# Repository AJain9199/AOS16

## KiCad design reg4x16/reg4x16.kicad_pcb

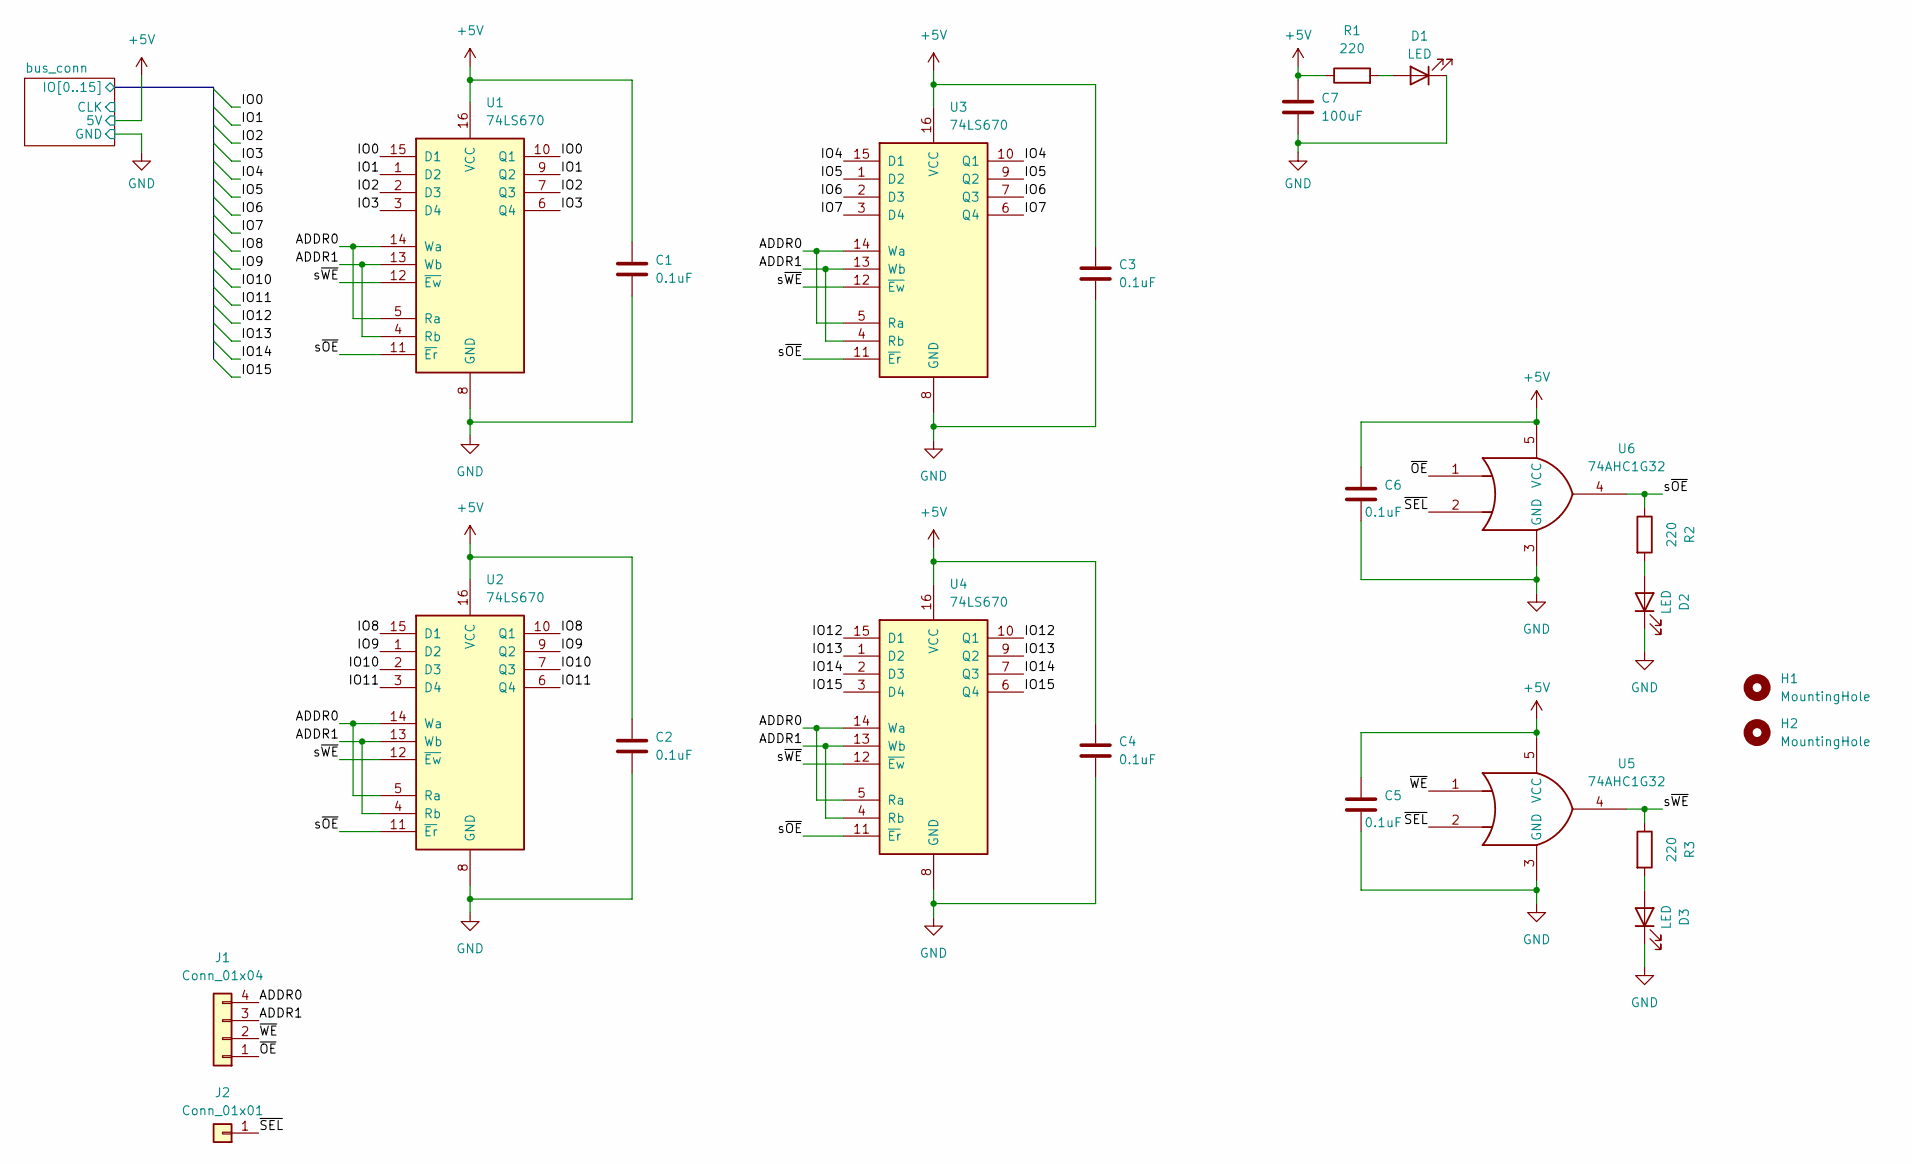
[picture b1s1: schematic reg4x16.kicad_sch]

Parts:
C1, C2, C3, C4, C5, C6: 0.1uF; C_0603_1608Metric
C7: 100uF; CP_Elec_5x5.3
D1, D2, D3: LED; LED_0603_1608Metric
H1, H2: MountingHole; MountingHole_2.2mm_M2
J1: Conn_01x04; PinHeader_1x04_P2.54mm_Vertical
J2: Conn_01x01; PinHeader_1x01_P2.54mm_Horizontal
R1, R2, R3: 220; R_0603_1608Metric
U1, U2, U3, U4: 74LS670; SOIC-16_3.9x9.9mm_P1.27mm
U5, U6: 74AHC1G32; SOT-23-5

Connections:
+5V: C1.1, C2.1, C3.1, C4.1, C5.1, C6.1, C7.1, R1.1, U1.16 (VCC), U2.16 (VCC), U3.16 (VCC), U4.16 (VCC), U5.5 (VCC), U6.5 (VCC); also elsewhere on the board
/ADDR0: J1.4, U1.5 (Ra), U1.14 (Wa), U2.5 (Ra), U2.14 (Wa), U3.5 (Ra), U3.14 (Wa), U4.5 (Ra), U4.14 (Wa)
/ADDR1: J1.3, U1.4 (Rb), U1.13 (Wb), U2.4 (Rb), U2.13 (Wb), U3.4 (Rb), U3.13 (Wb), U4.4 (Rb), U4.13 (Wb)
/bus_conn/IO0: U1.10 (Q1), U1.15 (D1); also elsewhere on the board
/bus_conn/IO1: U1.1 (D2), U1.9 (Q2); also elsewhere on the board
/bus_conn/IO2: U1.2 (D3), U1.7 (Q3); also elsewhere on the board
/bus_conn/IO3: U1.3 (D4), U1.6 (Q4); also elsewhere on the board
/bus_conn/IO4: U3.10 (Q1), U3.15 (D1); also elsewhere on the board
/bus_conn/IO5: U3.1 (D2), U3.9 (Q2); also elsewhere on the board
/bus_conn/IO6: U3.2 (D3), U3.7 (Q3); also elsewhere on the board
/bus_conn/IO7: U3.3 (D4), U3.6 (Q4); also elsewhere on the board
/bus_conn/IO8: U2.10 (Q1), U2.15 (D1); also elsewhere on the board
/bus_conn/IO9: U2.1 (D2), U2.9 (Q2); also elsewhere on the board
/bus_conn/IO10: U2.2 (D3), U2.7 (Q3); also elsewhere on the board
/bus_conn/IO11: U2.3 (D4), U2.6 (Q4); also elsewhere on the board
/bus_conn/IO12: U4.10 (Q1), U4.15 (D1); also elsewhere on the board
/bus_conn/IO13: U4.1 (D2), U4.9 (Q2); also elsewhere on the board
/bus_conn/IO14: U4.2 (D3), U4.7 (Q3); also elsewhere on the board
/bus_conn/IO15: U4.3 (D4), U4.6 (Q4); also elsewhere on the board
/s~OE: R2.1, U1.11 (~Er), U2.11 (~Er), U3.11 (~Er), U4.11 (~Er), U6.4
/s~WE: R3.1, U1.12 (~Ew), U2.12 (~Ew), U3.12 (~Ew), U4.12 (~Ew), U5.4
/~OE: J1.1, U6.1
/~SEL: J2.1, U5.2, U6.2
/~WE: J1.2, U5.1
GND: C1.2, C2.2, C3.2, C4.2, C5.2, C6.2, C7.2, D1.1 (K), D2.1 (K), D3.1 (K), U1.8 (GND), U2.8 (GND), U3.8 (GND), U4.8 (GND), U5.3 (GND), U6.3 (GND); also elsewhere on the board
unnamed: D1.2 (A), R1.2
unnamed: D2.2 (A), R2.2
unnamed: D3.2 (A), R3.2

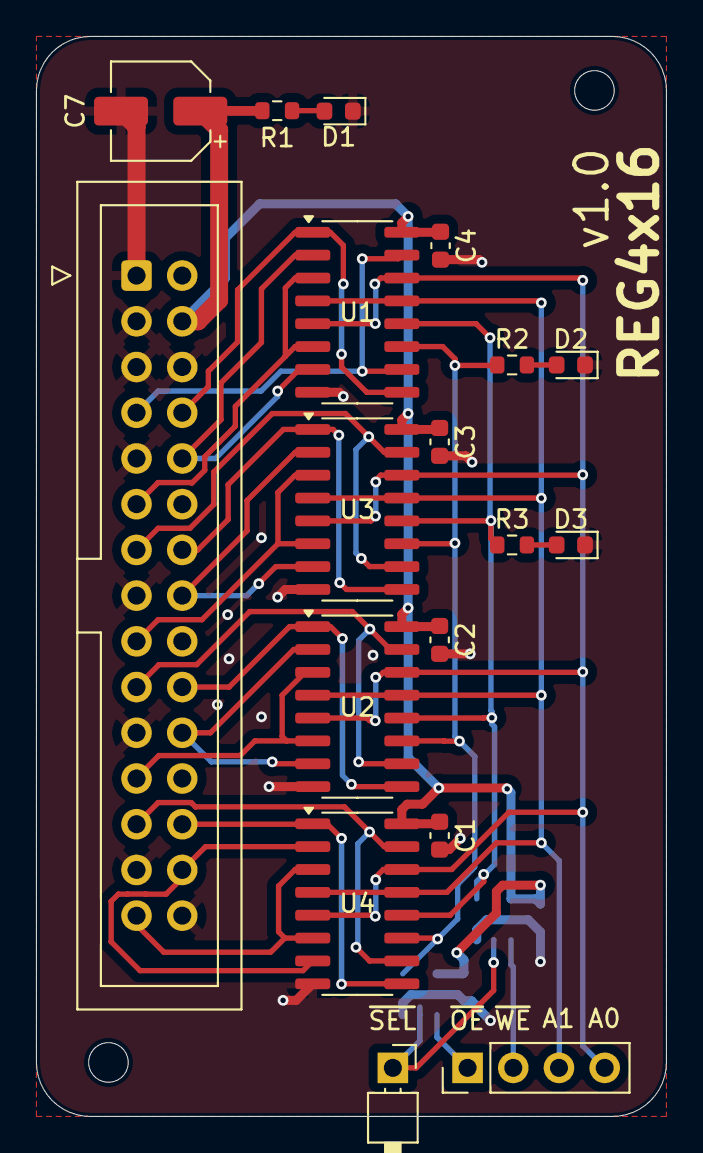
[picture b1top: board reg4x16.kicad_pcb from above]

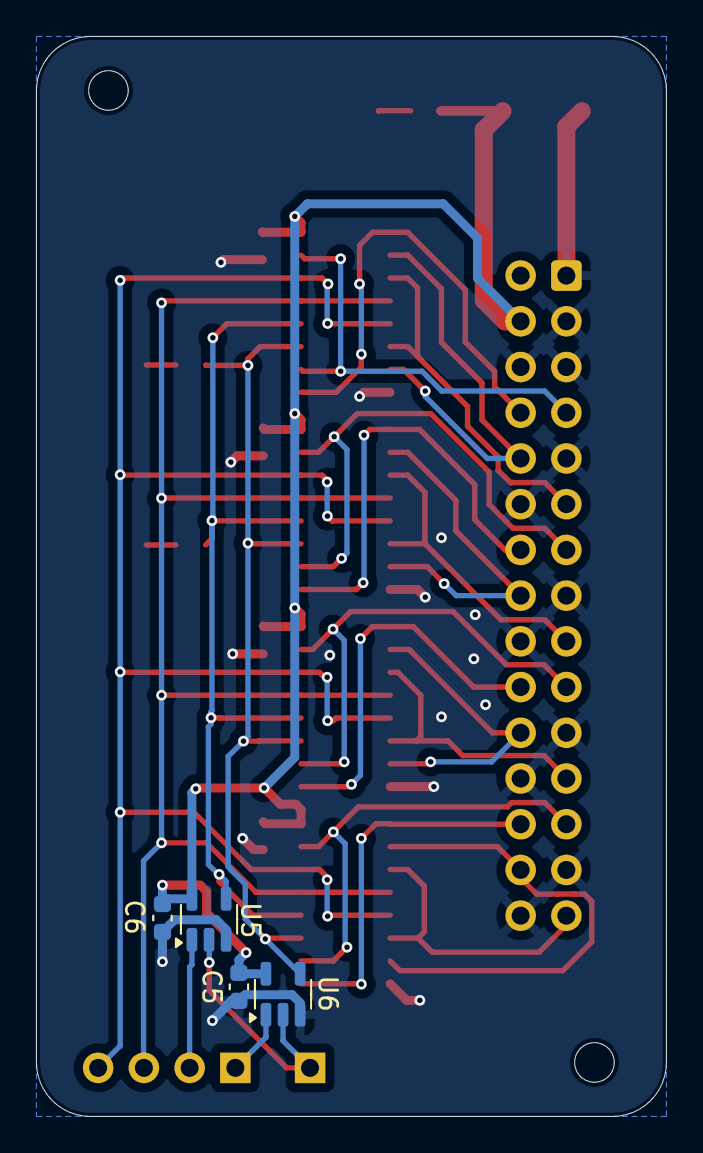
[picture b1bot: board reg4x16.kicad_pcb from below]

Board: 2 copper layers, 35.0 x 60.0 mm, 24 parts (4 on the bottom side), 28 nets.

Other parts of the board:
J3: Conn_02x15_Odd_Even; IDC-Header_2x15_P2.54mm_Vertical

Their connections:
+5V: J3.4; also elsewhere on the board
/bus_conn/IO0: J3.7; also elsewhere on the board
/bus_conn/IO1: J3.8; also elsewhere on the board
/bus_conn/IO2: J3.10; also elsewhere on the board
/bus_conn/IO3: J3.11; also elsewhere on the board
/bus_conn/IO4: J3.13; also elsewhere on the board
/bus_conn/IO5: J3.14; also elsewhere on the board
/bus_conn/IO6: J3.16; also elsewhere on the board
/bus_conn/IO7: J3.17; also elsewhere on the board
/bus_conn/IO8: J3.19; also elsewhere on the board
/bus_conn/IO9: J3.20; also elsewhere on the board
/bus_conn/IO10: J3.22; also elsewhere on the board
/bus_conn/IO11: J3.23; also elsewhere on the board
/bus_conn/IO12: J3.25; also elsewhere on the board
/bus_conn/IO13: J3.26; also elsewhere on the board
/bus_conn/IO14: J3.28; also elsewhere on the board
/bus_conn/IO15: J3.29; also elsewhere on the board
GND: J3.1, J3.3, J3.5, J3.6, J3.9, J3.12, J3.15, J3.18, J3.21, J3.24, J3.27, J3.30; also elsewhere on the board
